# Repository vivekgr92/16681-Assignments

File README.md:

# 16681-MRSD
All assignmentsrelated to MRSD project course

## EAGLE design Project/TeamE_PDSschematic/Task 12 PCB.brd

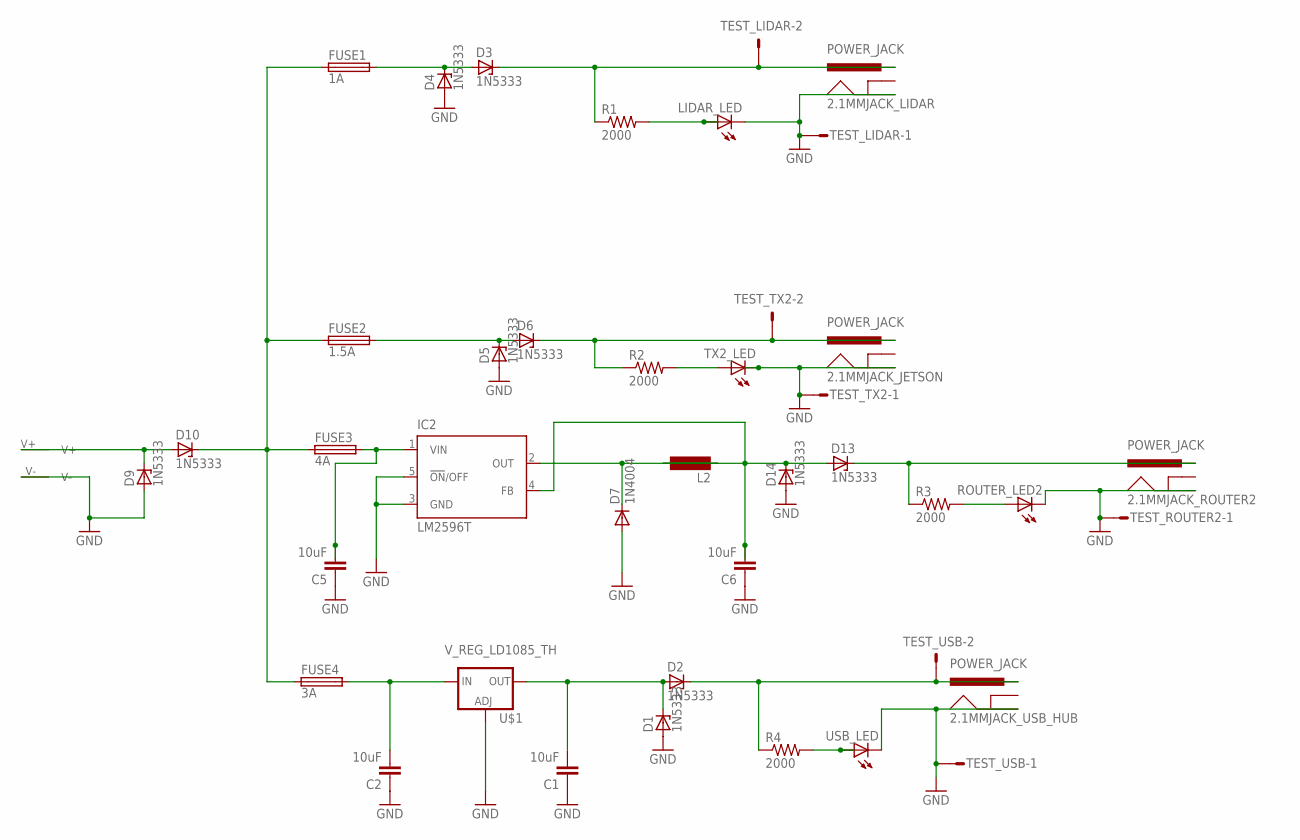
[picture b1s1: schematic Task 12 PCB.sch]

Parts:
2.1MMJACK_JETSON, 2.1MMJACK_LIDAR, 2.1MMJACK_ROUTER2, 2.1MMJACK_USB_HUB: POWER_JACK; POWER_JACK_PTH
C1, C2, C5, C6: 10uF; 1206
D1, D2, D3, D4, D5, D6, D9, D10, D13, D14: 1N5333; C1702-15
D7: 1N4004; DO41-10
FUSE1: 1A; LITTLEFUSE
FUSE2: 1.5A; LITTLEFUSE
FUSE3: 4A; LITTLEFUSE
FUSE4: 3A; LITTLEFUSE
IC2: LM2596T; T05D
L2: SD12K-82
LIDAR_LED: LED_E; LED_1206
R1, R2, R3, R4: 2000; M1206
ROUTER_LED2: LED_E; LED_1206
TEST_LIDAR: MA02S; 02PA
TEST_ROUTER2: MA02S; 02PA
TEST_TX2: MA02S; 02PA
TEST_USB: MA02S; 02PA
TX2_LED: LED_E; LED_1206
U$1: V_REG_LD1085_TH; TO-220-ALT
U$2: XT_60_DEVICEONLY; BOARD_CONNECTOR
USB_LED: LED_E; LED_1206

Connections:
GND: 2.1MMJACK_JETSON.GND, 2.1MMJACK_LIDAR.GND, 2.1MMJACK_ROUTER2.GND, 2.1MMJACK_USB_HUB.GND, C1.1, C2.1, C5.1, C6.1, D1.A, D4.A, D5.A, D7.A, D9.A, D14.A, IC2.3 (GND), IC2.5 (!ON!/OFF), LIDAR_LED.C, ROUTER_LED2.C, TEST_LIDAR.1, TEST_ROUTER2.1, TEST_TX2.1, TEST_USB.1, TX2_LED.C, U$1.GND (ADJ), U$2.V-, USB_LED.C
unnamed: LIDAR_LED.A, R1.2
unnamed: 2.1MMJACK_USB_HUB.PWR, D2.C, R4.1, TEST_USB.2
unnamed: 2.1MMJACK_LIDAR.PWR, D3.C, R1.1, TEST_LIDAR.2
unnamed: C2.2, FUSE4.2, U$1.IN
unnamed: R2.2, TX2_LED.A
unnamed: 2.1MMJACK_JETSON.PWR, D6.C, R2.1, TEST_TX2.2
unnamed: R4.2, USB_LED.A
unnamed: C1.2, D1.C, D2.A, U$1.OUT
unnamed: D3.A, D4.C, FUSE1.2
unnamed: D5.C, D6.A, FUSE2.2
unnamed: D10.C, FUSE1.1, FUSE2.1, FUSE3.1, FUSE4.1
unnamed: D9.C, D10.A, U$2.V+
unnamed: C5.2, FUSE3.2, IC2.1 (VIN)
unnamed: D7.C, IC2.2 (OUT), L2.1
unnamed: C6.2, D13.A, D14.C, IC2.4 (FB), L2.2
unnamed: R3.2, ROUTER_LED2.A
unnamed: 2.1MMJACK_ROUTER2.PWR, D13.C, R3.1

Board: 2 copper layers, 39 parts (0 on the bottom side), 18 nets, no tracks yet.

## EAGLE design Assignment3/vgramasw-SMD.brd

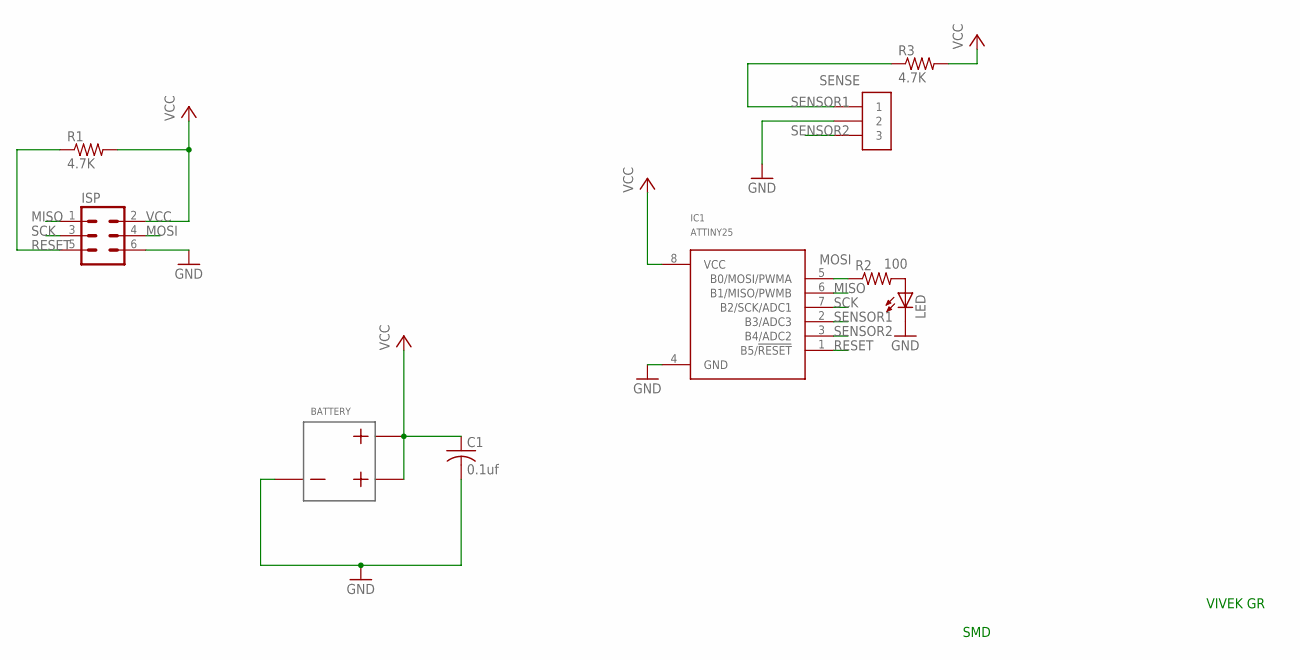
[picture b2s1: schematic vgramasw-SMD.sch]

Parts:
BATTERY: BATTERYSM_BA2032; BA2032SM
C1: 0.1uf; C0402
IC1: ATTINY25; 8S1
ISP: 6PINCON_ISPSM_6PIN; SM6PIN
LED: LEDSMLED; CHIPLED_0603
R1, R3: 4.7K; R0402
R2: 100; R0402
SENSE: 3PINCONSM_3PIN; SM3PIN

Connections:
GND: BATTERY.1, C1.2, IC1.4 (GND), ISP.6, LED.C, SENSE.2
MISO: IC1.6 (B1/MISO/PWMB), ISP.1
MOSI: IC1.5 (B0/MOSI/PWMA), ISP.4, R2.1
unnamed: LED.A, R2.2
RESET: IC1.1 (B5/!RESET), ISP.5, R1.1
SCK: IC1.7 (B2/SCK/ADC1), ISP.3
SENSOR1: IC1.2 (B3/ADC3), R3.1, SENSE.1
SENSOR2: IC1.3 (B4/ADC2), SENSE.3
VCC: BATTERY.2, BATTERY.3, C1.1, IC1.8 (VCC), ISP.2, R1.2, R3.2

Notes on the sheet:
SMD
VIVEK GR

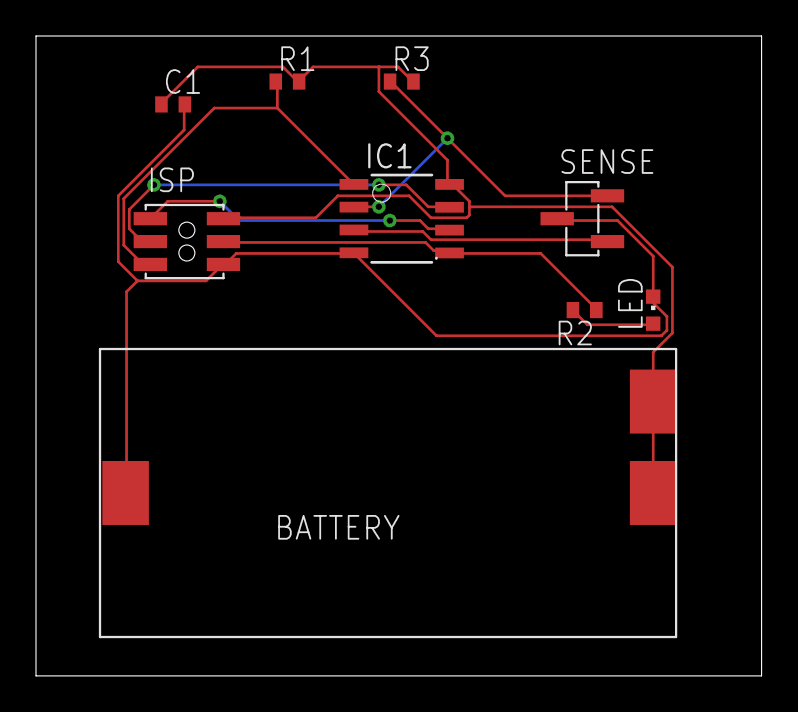
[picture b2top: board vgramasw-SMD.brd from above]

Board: 2 copper layers, 40.3 x 35.5 mm, 9 parts (0 on the bottom side), 9 nets.

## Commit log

2017-11-12 Add all assingments related to MRSD project course
2017-11-12 ADD Part3 ROS
2020-06-10 Created using Colaboratory

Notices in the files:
parts and their libraries:
SparkFun-Connectors: Licensing: Creative Commons ShareAlike 4.0 International - https://creativecommons.org/licenses/by-sa/4.0
